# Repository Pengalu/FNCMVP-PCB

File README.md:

# FNCMVP-PCB
### FluidNC Minimum Viable Product PCB

Testing repository for designing a CNC-Controller using the FluidNC firmware without special features to expand upon.

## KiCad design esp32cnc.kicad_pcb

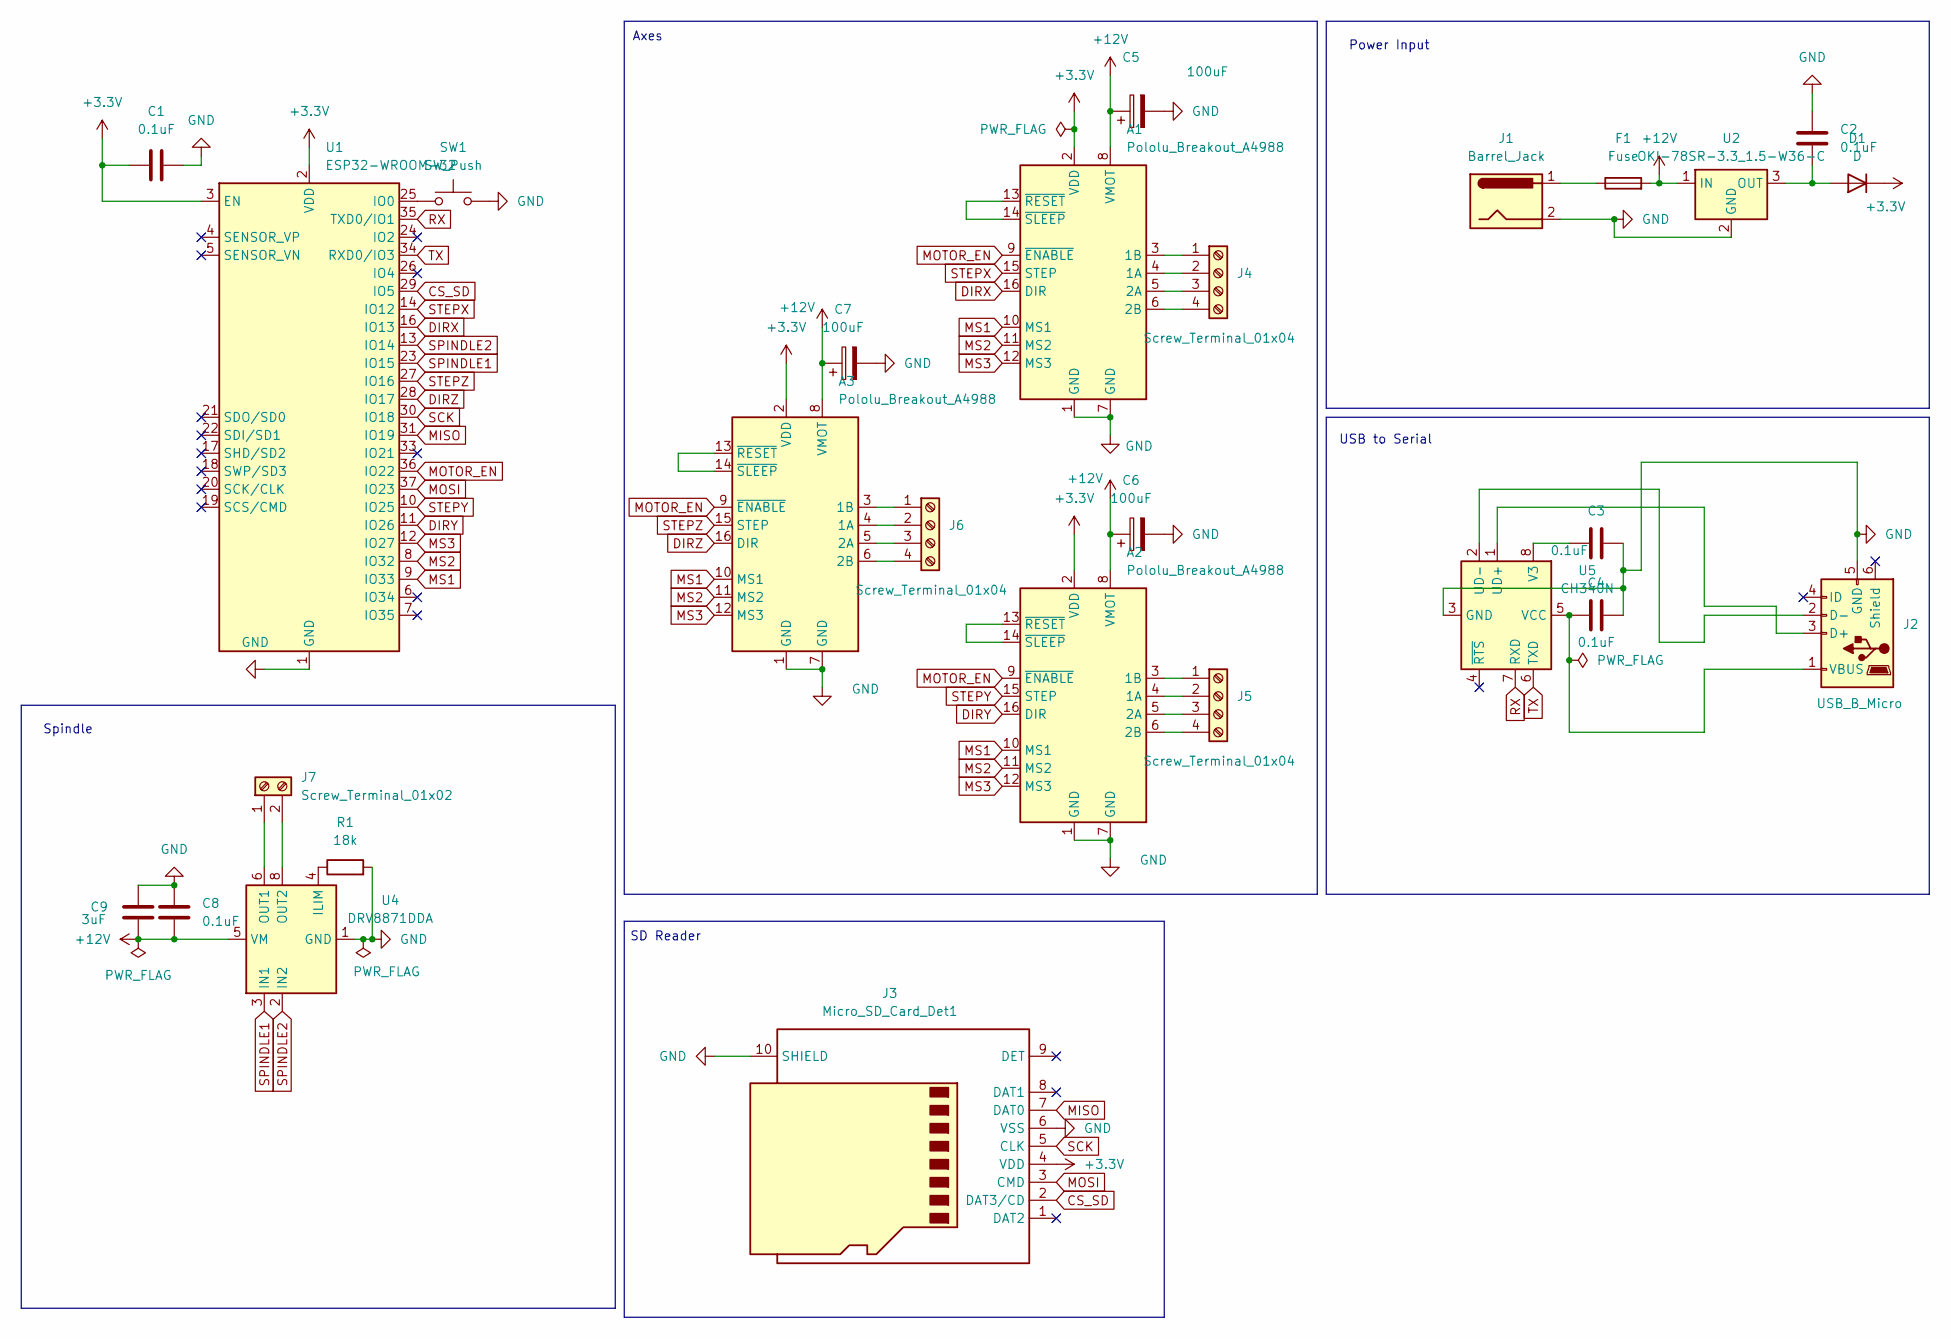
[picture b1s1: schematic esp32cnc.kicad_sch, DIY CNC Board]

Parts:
A1, A2, A3: Pololu_Breakout_A4988; Pololu_Breakout-16_15.2x20.3mm
C1, C2, C3, C4, C8: 0.1uF; C_Radial_D4.0mm_H5.0mm_P1.50mm
C5, C6, C7: 100uF; CP_Radial_D5.0mm_P2.50mm
C9: 3uF; C_Radial_D4.0mm_H5.0mm_P1.50mm
D1: D; D_T-1_P12.70mm_Horizontal
F1: Fuse; Fuseholder_TR5_Littelfuse_No560_No460
J1: Barrel_Jack; BarrelJack_SwitchcraftConxall_RAPC10U_Horizontal
J2: USB_B_Micro; USB_Micro-AB_Molex_47590-0001
J3: Micro_SD_Card_Det1; microSD_HC_Molex_47219-2001
J4, J5, J6: Screw_Terminal_01x04; TerminalBlock_WAGO_236-104_1x04_P5.00mm_45Degree
J7: Screw_Terminal_01x02; TerminalBlock_Philmore_TB132_1x02_P5.00mm_Horizontal
R1: 18k
SW1: SW_Push
U1: ESP32-WROOM-32
U2: OKI-78SR-3.3_1.5-W36-C; Converter_DCDC_Murata_OKI-78SR_Vertical
U4: DRV8871DDA; Texas_HTSOP-8-1EP_3.9x4.9mm_P1.27mm_EP2.95x4.9mm_Mask2.4x3.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
U5: CH340N; SOP-8_3.9x4.9mm_P1.27mm

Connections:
+3.3V: A1.2 (VDD), A2.2 (VDD), A3.2 (VDD), C1.1, D1.1 (K), J3.4 (VDD), U1.2 (VDD), U1.3 (EN)
+12V: A1.8 (VMOT), A2.8 (VMOT), A3.8 (VMOT), C5.1, C6.1, C7.1, C8.2, C9.2, F1.2, U2.1 (IN), U4.5 (VM)
CS_SD: J3.2 (DAT3/CD), U1.29 (IO5)
DIRX: A1.16 (DIR), U1.16 (IO13)
DIRY: A2.16 (DIR), U1.11 (IO26)
DIRZ: A3.16 (DIR), U1.28 (IO17)
GND: A1.1 (GND), A1.7 (GND), A2.1 (GND), A2.7 (GND), A3.1 (GND), A3.7 (GND), C1.2, C2.1, C3.1, C4.1, C5.2, C6.2, C7.2, C8.1, C9.1, J1.2, J2.5 (GND), J3.6 (VSS), J3.10 (SHIELD), R1.2, SW1.2, U1.1 (GND), U1.15 (GND), U1.38 (GND), U1.39 (GND), U2.2 (GND), U4.1 (GND), U4.7 (GND), U4.9 (GND), U5.3 (GND)
MISO: J3.7 (DAT0), U1.31 (IO19)
MOSI: J3.3 (CMD), U1.37 (IO23)
MOTOR_EN: A1.9 (~ENABLE), A2.9 (~ENABLE), A3.9 (~ENABLE), U1.36 (IO22)
MS1: A1.10 (MS1), A2.10 (MS1), A3.10 (MS1), U1.9 (IO33)
MS2: A1.11 (MS2), A2.11 (MS2), A3.11 (MS2), U1.8 (IO32)
MS3: A1.12 (MS3), A2.12 (MS3), A3.12 (MS3), U1.12 (IO27)
unnamed: A1.4 (1A), J4.2
unnamed: A1.3 (1B), J4.1
unnamed: A1.5 (2A), J4.3
unnamed: A1.6 (2B), J4.4
unnamed: A1.13 (~RESET), A1.14 (~SLEEP)
unnamed: A2.4 (1A), J5.2
unnamed: A2.3 (1B), J5.1
unnamed: A2.5 (2A), J5.3
unnamed: A2.6 (2B), J5.4
unnamed: A2.13 (~RESET), A2.14 (~SLEEP)
unnamed: A3.4 (1A), J6.2
unnamed: A3.3 (1B), J6.1
unnamed: A3.5 (2A), J6.3
unnamed: A3.6 (2B), J6.4
unnamed: A3.13 (~RESET), A3.14 (~SLEEP)
unnamed: C2.2, D1.2 (A), U2.3 (OUT)
unnamed: F1.1, J1.1
unnamed: J2.3 (D+), U5.1 (UD+)
unnamed: J2.2 (D-), U5.2 (UD-)
unnamed: C4.2, J2.1 (VBUS), U5.5 (VCC)
unnamed: J7.1, U4.6 (OUT1)
unnamed: J7.2, U4.8 (OUT2)
unnamed: SW1.1, U1.25 (IO0)
unnamed: R1.1, U4.4 (ILIM)
unnamed: C3.2, U5.8 (V3)
RX: U1.35 (TXD0/IO1), U5.7 (RXD)
SCK: J3.5 (CLK), U1.30 (IO18)
SPINDLE1: U1.23 (IO15), U4.3 (IN1)
SPINDLE2: U1.13 (IO14), U4.2 (IN2)
STEPX: A1.15 (STEP), U1.14 (IO12)
STEPY: A2.15 (STEP), U1.10 (IO25)
STEPZ: A3.15 (STEP), U1.27 (IO16)
TX: U1.34 (RXD0/IO3), U5.6 (TXD)

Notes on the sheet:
Power Input
Axes
SD Reader
USB to Serial
Spindle

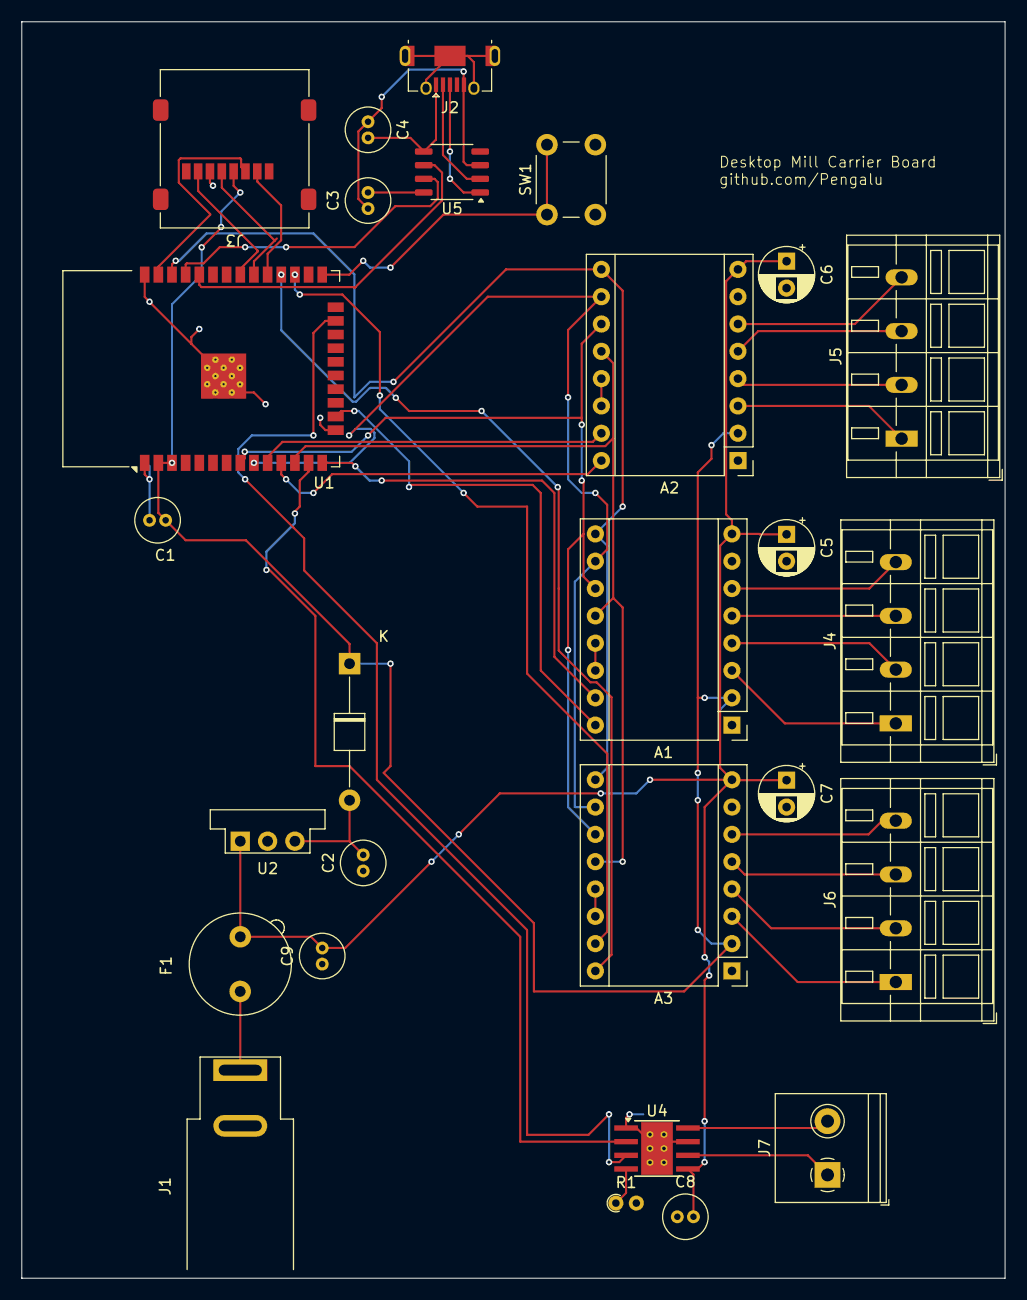
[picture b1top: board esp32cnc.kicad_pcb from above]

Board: 2 copper layers, 91.4 x 116.8 mm, 27 parts (0 on the bottom side), 46 nets.

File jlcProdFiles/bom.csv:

Designator,Footprint,Quantity,Value,LCSC Part #
"A1, A2, A3",Pololu_Breakout-16_15.2x20.3mm,3,Pololu_Breakout_A4988,
"C1, C2, C3, C4, C8",C_Radial_D4.0mm_H5.0mm_P1.50mm,5,0.1uF,
"C5, C6, C7",CP_Radial_D5.0mm_P2.50mm,3,100uF,
C9,C_Radial_D4.0mm_H5.0mm_P1.50mm,1,3uF,
D1,D_T-1_P12.70mm_Horizontal,1,D,
F1,Fuseholder_TR5_Littelfuse_No560_No460,1,Fuse,
J1,BarrelJack_SwitchcraftConxall_RAPC10U_Horizontal,1,Barrel_Jack,
J2,USB_Micro-AB_Molex_47590-0001,1,USB_B_Micro,
J3,microSD_HC_Molex_47219-2001,1,Micro_SD_Card_Det1,
"J4, J5, J6",TerminalBlock_WAGO_236-104_1x04_P5.00mm_45Degree,3,Screw_Terminal_01x04,
J7,TerminalBlock_Philmore_TB132_1x02_P5.00mm_Horizontal,1,Screw_Terminal_01x02,
U1,ESP32-WROOM-32,1,ESP32-WROOM-32,
U2,Converter_DCDC_Murata_OKI-78SR_Vertical,1,OKI-78SR-3.3_1.5-W36-C,
U4,Texas_HTSOP-8-1EP_3.9x4.9mm_P1.27mm_EP2.95x4.9mm_Mask2.4x3.1mm_ThermalVias,1,DRV8871DDA,
U5,SOP-8_3.9x4.9mm_P1.27mm,1,CH340N,

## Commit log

2024-11-24 Init
2024-11-25 generate bom
2024-11-25 bom uploaded to git
2024-11-25 change to ch340n
2024-11-25 rotate SD-Card
2024-11-26 prepped for manufacturing
2024-11-26 cleanup
2025-01-23 flipped rx/tx, added boot button, added ILM resistor
